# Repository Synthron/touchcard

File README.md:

# TouchCard

Business Card with capacitive touch field

Based on STM32

Inspired by [xenua](https://xenua.me/)

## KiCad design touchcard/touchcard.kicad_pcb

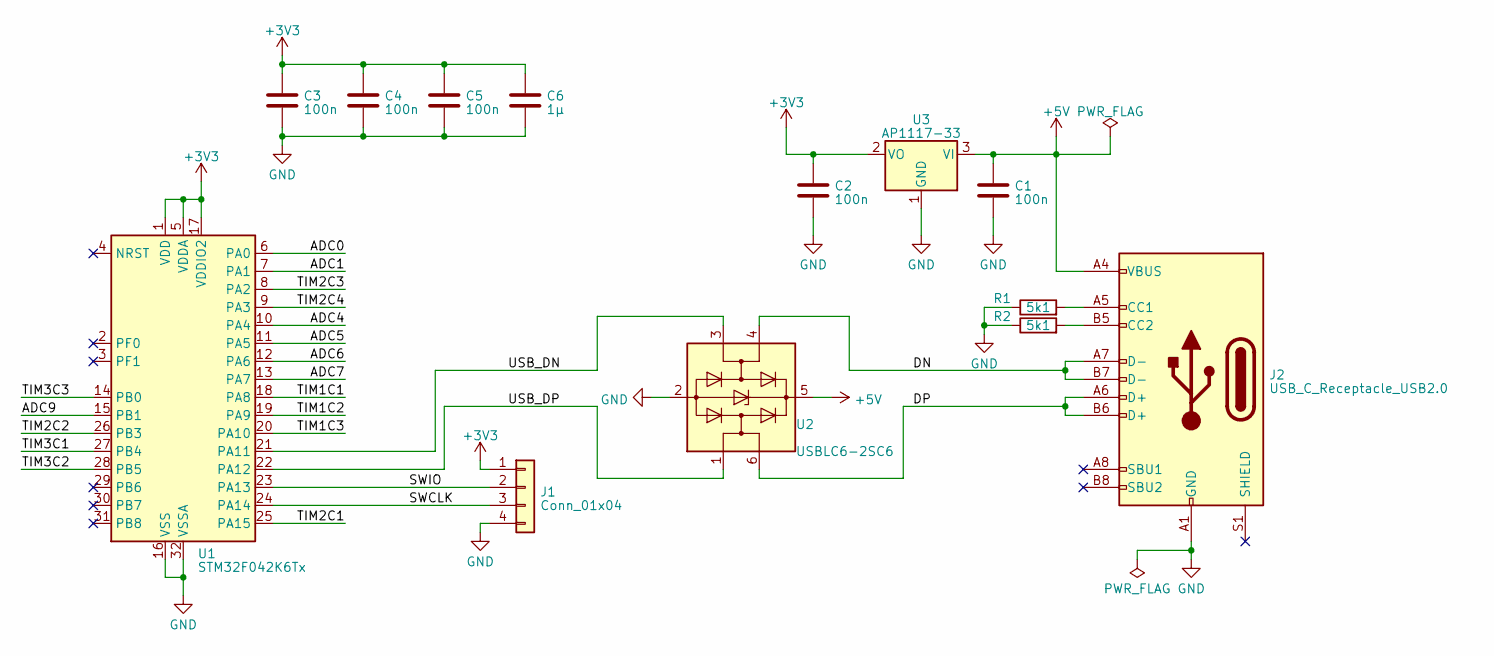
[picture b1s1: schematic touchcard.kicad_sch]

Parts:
C1, C2, C3, C4, C5: 100n; 0603_1608Metric_Pad1.08x0.95mm_MidMount
C6: 1µ; 0603_1608Metric_Pad1.08x0.95mm_MidMount
J1: Conn_01x04; SWD_PADS
J2: USB_C_Receptacle_USB2.0; USB_C_PCB
R1, R2: 5k1; 0603_1608Metric_Pad1.08x0.95mm_MidMount
U1: STM32F042K6Tx; LQFP-32_7x7mm_P0.8mm_midmount
U2: USBLC6-2SC6; SOT-23-6_MidMount
U3: AP1117-33; SOT-223-3_TabPin2_MidMount

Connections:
+3V3: C2.1, C3.1, C4.1, C5.1, C6.1, J1.1, U1.1 (VDD), U1.5 (VDDA), U1.17 (VDDIO2), U3.2 (VO)
+5V: C1.1, J2.A4 (VBUS), J2.A9 (VBUS), J2.B4 (VBUS), J2.B9 (VBUS), U2.5 (VBUS), U3.3 (VI)
/ADC0: U1.6 (PA0)
/ADC1: U1.7 (PA1)
/ADC4: U1.10 (PA4)
/ADC5: U1.11 (PA5)
/ADC6: U1.12 (PA6)
/ADC7: U1.13 (PA7)
/ADC9: U1.15 (PB1)
/DN: J2.A7 (D-), J2.B7 (D-), U2.4 (I/O2)
/DP: J2.A6 (D+), J2.B6 (D+), U2.6 (I/O1)
/SWCLK: J1.3, U1.24 (PA14)
/SWIO: J1.2, U1.23 (PA13)
/TIM1C1: U1.18 (PA8)
/TIM1C2: U1.19 (PA9)
/TIM1C3: U1.20 (PA10)
/TIM2C1: U1.25 (PA15)
/TIM2C2: U1.26 (PB3)
/TIM2C3: U1.8 (PA2)
/TIM2C4: U1.9 (PA3)
/TIM3C1: U1.27 (PB4)
/TIM3C2: U1.28 (PB5)
/TIM3C3: U1.14 (PB0)
/USB_DN: U1.21 (PA11), U2.3 (I/O2)
/USB_DP: U1.22 (PA12), U2.1 (I/O1)
GND: C1.2, C2.2, C3.2, C4.2, C5.2, C6.2, J1.4, J2.A1 (GND), J2.A12 (GND), J2.B1 (GND), J2.B12 (GND), R1.1, R2.1, U1.16 (VSS), U1.32 (VSSA), U2.2 (GND), U3.1 (GND)
unnamed: J2.A5 (CC1), R1.2
unnamed: J2.B5 (CC2), R2.2

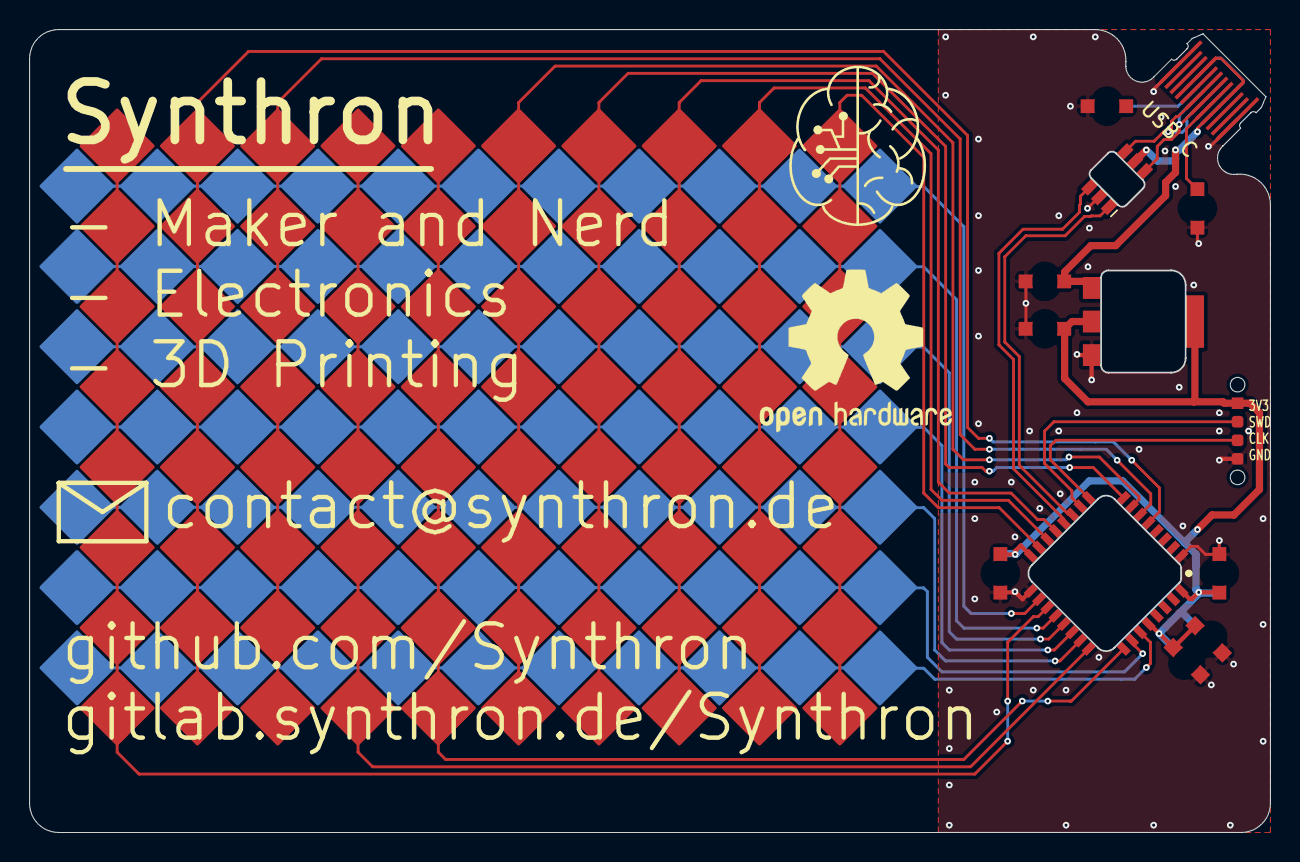
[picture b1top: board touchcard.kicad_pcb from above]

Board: 2 copper layers, 84.9 x 54.9 mm, 13 parts (1 on the bottom side), 11 nets.

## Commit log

2023-06-12 Initial Commit Start of Schematic and PCB Initial Version of IOC File
2023-06-13 Finalize Schematic and Layout
2023-06-20 PCB Review
2023-06-20 Readme Typo fix
2023-07-26 Initial Code for Touchpad
2024-06-03 code update
